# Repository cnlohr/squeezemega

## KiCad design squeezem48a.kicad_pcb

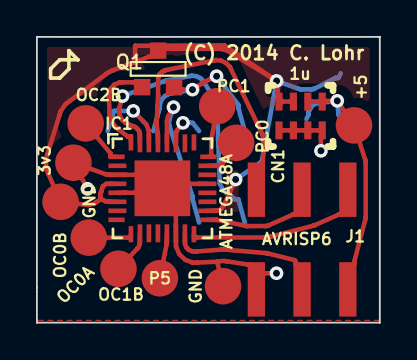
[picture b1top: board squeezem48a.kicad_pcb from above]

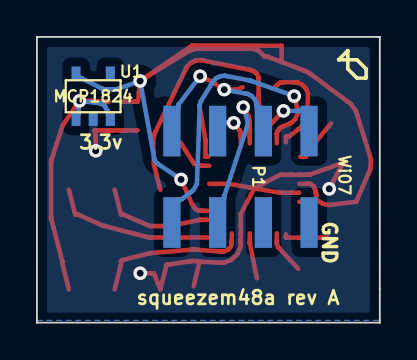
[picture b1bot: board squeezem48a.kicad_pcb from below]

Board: 2 copper layers, 19.0 x 15.9 mm, 16 parts (2 on the bottom side), 19 nets.

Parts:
CN1: 1u; NETWORK1206
IC1: ATMEGA48A; QFN32
J1: AVRISP6; RIBBON6SMT
P1: Wi07; RIBBON8SMT
P2: OC2B; .1SMTPIN
P3: OC0B; .1SMTPIN
P4: OC0A; .1SMTPIN
P5: OC1B; .1SMTPIN
P6: PC1; .1SMTPIN
P7: PC0; .1SMTPIN
P8: +5; .1SMTPIN
P9: 3v3; .1SMTPIN
P10, P11: GND; .1SMTPIN
Q1: 3VGATE-1A-PMOS; SOT23GDS
U1: MCP1824; SOT23-5

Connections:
+3.3V: CN1.7, CN1.8, IC1.4, IC1.6, IC1.18, P10.1, Q1.D, U1.5
+5V: CN1.5, CN1.6, J1.2, P8.1, U1.1, U1.3
GND: CN1.1, CN1.2, CN1.3, CN1.4, IC1.3, IC1.5, IC1.14, IC1.21, IC1.33, J1.6, P1.2, P9.1, P11.1, U1.2
unnamed: IC1.10, P4.1
unnamed: IC1.30, P1.1
unnamed: IC1.31, P1.8
unnamed: IC1.28, P1.6
unnamed: IC1.9, P3.1
unnamed: IC1.23, P7.1
unnamed: IC1.1, P2.1
unnamed: P1.3, P1.7, Q1.S
unnamed: IC1.27, P1.5
unnamed: IC1.32, Q1.G
unnamed: IC1.13, P5.1
unnamed: IC1.24, P6.1
unnamed: IC1.16, J1.1
unnamed: IC1.17, J1.3
unnamed: IC1.29, J1.5
unnamed: IC1.15, J1.4

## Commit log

2014-09-27 add files for mega
2014-10-24 update to rev A

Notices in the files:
squeezem48a.kicad_pcb:
(C) 2014 C. Lohr
